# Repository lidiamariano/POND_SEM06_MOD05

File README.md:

# Atividade Ponderada - Placa de circuito impresso com Raspberry Pi Pico
## Descrição clara dos arquivos
- KiCad-RP-Pico-main: esse arquivo contém a biblioteca para ser colocada no Kicad que possui a placa Raspberry pi Pico
- POND_MOD05SEM06: essa pasta contém a atividadede fato. Nela hão os seguintes arquivos:
  - POND_MOD05SEM06-backups: pasta que possui todas as versões de arquivos feitas até a versão final, ou seja, todos os salvamentos.
  - fp-info-cache: arquivo que possui todos os elementos implementados
  - POND_MOD05SEM06.kicad_pcb: arquivo que possui a placa em formato pcb
  - POND_MOD05SEM06.kicad_sch: arquivo que possui o desenho esquemático da placa.
  - POND_MOD05SEM06.kicad_pro: arquivo de configurações locais do projeto e armazenará configurações que devem ser consideradas “locais” para o seu computador

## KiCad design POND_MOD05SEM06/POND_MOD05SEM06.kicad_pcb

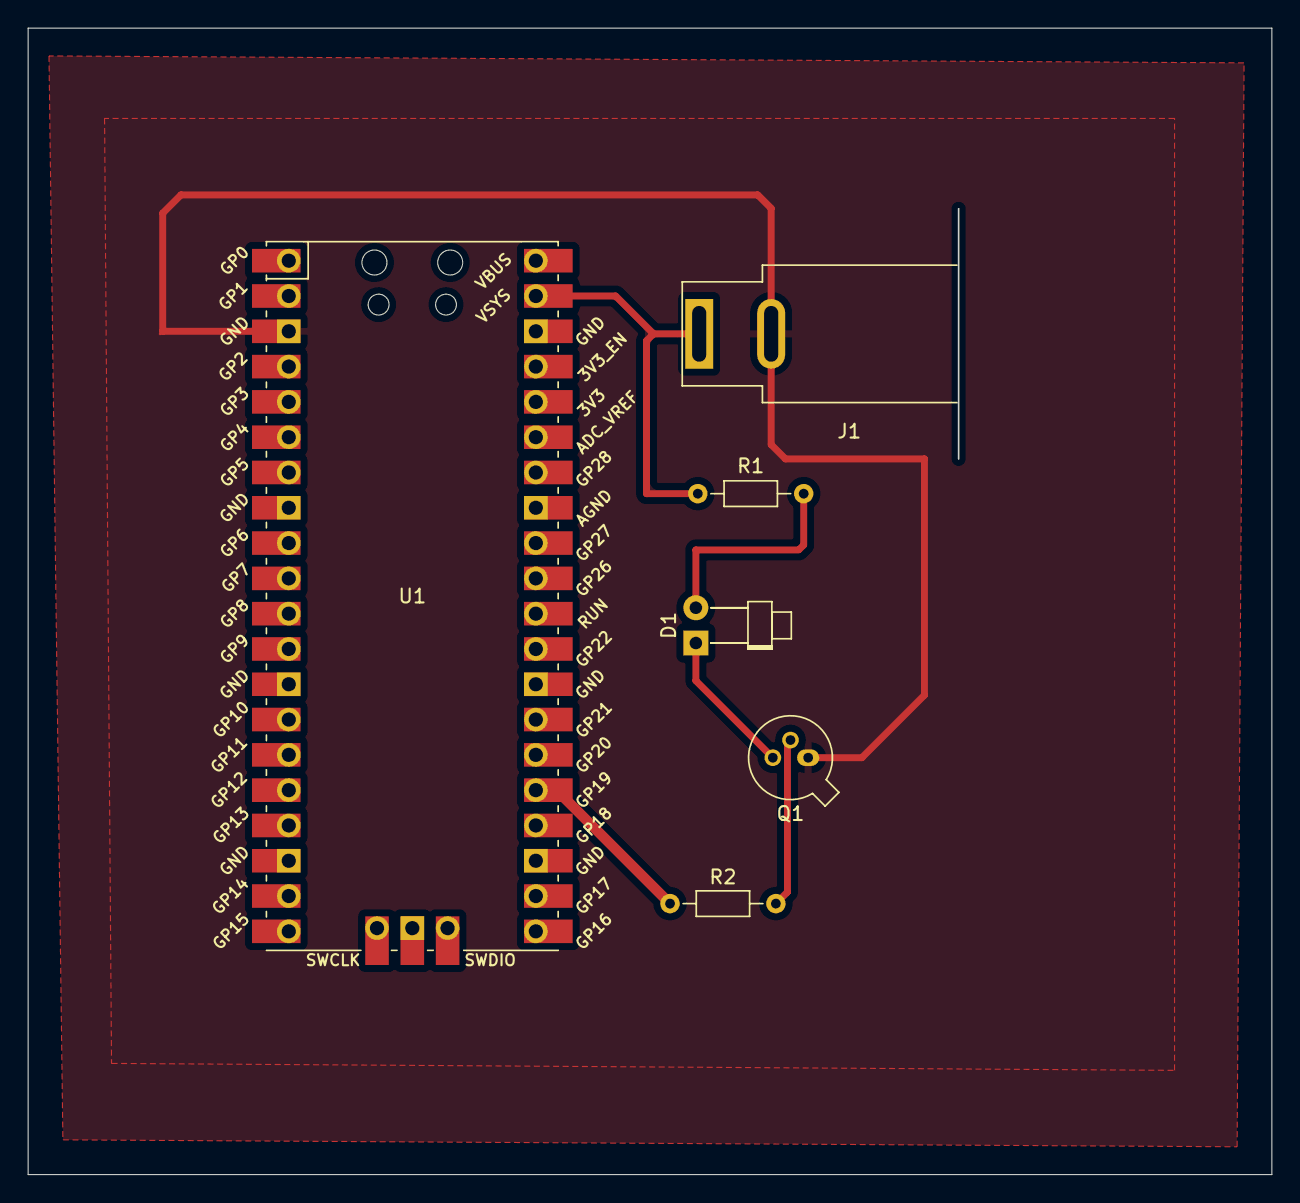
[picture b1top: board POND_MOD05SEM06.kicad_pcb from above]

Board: 2 copper layers, 89.4 x 82.4 mm, 6 parts (0 on the bottom side), 6 nets.

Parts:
D1: LED; LED_D1.8mm_W1.8mm_H2.4mm_Horizontal_O3.81mm_Z8.2mm
J1: Barrel_Jack; BarrelJack_SwitchcraftConxall_RAPC10U_Horizontal
Q1: BC107; TO-18-3
R1, R2: R_US; R_Axial_DIN0204_L3.6mm_D1.6mm_P7.62mm_Horizontal
U1: Pico; RPi_Pico_SMD_TH

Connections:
GND: J1.2, Q1.1 (E), U1.3 (GND)
unnamed: D1.2 (A), R1.2
unnamed: D1.1 (K), Q1.3 (C)
unnamed: Q1.2 (B), R2.2
unnamed: R2.1, U1.24 (GPIO18), U1.25 (GPIO19)
VCC: J1.1, R1.1, U1.39 (VSYS)

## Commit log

2024-03-31 feat: adiçao de arquivos
2024-03-31 feat: atualizacao de arquivos
2024-03-31 feat: retirando arquivos que nao devem ser considerados
